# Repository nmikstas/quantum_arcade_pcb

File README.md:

# quantum_arcade_pcb
Reproduction of the Atari Quantum Arcade PCB. The PCB is designed with Kicad. This project is now complete and verified working!

# Folder Structure
* BOM - Bill of materials
* gerbers - Gerber files
* Quantum_1B_GAL - Design and programming files for the GAL IC located at location 1B
* quantum_arcade_pcb - Kicad design files

# PCB Specifications
* Layers: 2
* Dimensions: 293mm X 531mm
* Different PCB Design: 1
* PCB Thickness: 1.6mm
* Surface Finish: HASL
* Castellated Holes: No
* Copper Weight: 1oz.

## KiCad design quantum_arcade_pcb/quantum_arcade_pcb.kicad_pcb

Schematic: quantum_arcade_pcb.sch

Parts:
A_3: LM324A; DIP14
A_5: LS157A; DIP16
A_7, A_8: LS194; DIP16
A_10: 082; DIP8
B_1: 137290; DIP20
B_2/3: POKEY; DDIP40
B_5: LS157B; DIP16
B_6: AVG; DDIP40
B_7, B_8: LS194; DIP16
B_9: AM6012; DIP20
B_10: LF13201; DIP16
B_11, B_12: MC1495LB; DIP14
C2, C3, C9, C10, C11, C14, C15, C16, C17, C18, C19, C20, C26, C27, C28, C31, C33, C34, C35, C36, C39, C40: .1uF; GenComp
C4: .01uF; CapSmall
C5, C6, C22, C23: ?; GenComp
C7, C24: ?; CapSmall
C8, C25: .047uF; CapInt
C12, C29: 39pf; CapSmall
C13, C30, C32: 100pf; CapSmall
C21: .0018uF; CapSmall
C37: 150pF; CapSmall
C38: 39pF; CapSmall
C41: .01uF; GenComp
C42: 10pF; CapSmall
C44, C46: 100uf 35V; Cap2
C45, C48: 22uf 25V; Cap1
C47: 22uf 35V; Cap3
C49, C64, C65, C67, C68, C69, C70, C71, C72, C73, C75, C78, C79, C81, C91, C92, C93, C94, C95, C96, C97, C98, C99, C100, C101, C102, C103, C104, C105, C106, C107, C108, C109, C110, C111, C112, C113, C114, C115, C116, C117, C118, C119, C120, C121, C122, C123, C124, C125, C126, C127, C128, C129: .1uf; GenComp
C51, C61: 1000pf 100V; GenComp
C52, C53, C54, C55, C56, C57, C58, C59, C60, C62: 1uf 50V; Cap1
C63: 220pf; GenComp
C74: 1uf; Cap1
C76: 100pf 100V; CapSmall
C77: 39pf 100V; CapSmall
C80: .022uf; GenComp
C82: 100uf 25V; Cap2
C83, C84, C85, C86, C87, C88, C89, C90: .01uf 25V; GenComp
C130: .047uf; GenComp
CR1: 1N914; Diode
CR3, CR4, CR6: 1N100; Diode
CR5: 1N754A; Diode
CR7: LED
C_3: LM324A; DIP14
C_5: LS157B; DIP16
C_7, C_8: LS194; DIP16
C_9: Spare16; DIP16
C_11, C_12: MC1495LA; DIP14
D/E_4: LS245; DIP20
D/E_11, D/E_12: 082; DIP8
D_1: LS138; DIP16
D_2/3: POKEY; DDIP40
D_5, D_6: 2KX8_RAM; DDIP24
D_7: LS175C; DIP16
D_8: LS273; DIP20
D_9: DAC_8; DIP16
D_10: 082; DIP8
E/F_4: LS245; DIP20
E_1: LS244A; DIP20
E_2, E_3: 8KX8_ROM; DIP28
E_5, E_6: 2KX8_RAM; DDIP24
E_7: LS157B; DIP16
E_9: Spare16; DIP16
E_10: LF13201; DIP16
F/H_4: LS04; DIP14
F/H_9: AM6012; DIP20
F_1: LS244B; DIP20
F_2, F_3: 8KX8_ROM; DIP28
F_5: LS32; DIP14
F_6: LS00; DIP14
F_7: S289; DIP16
F_8: LS175; DIP16
H/J_2, H/J_3: 8KX8_ROM; DIP28
H/J_4: LS138; DIP16
H_5: LS174; DIP16
H_6: S129; DIP16
H_7: LS00; DIP14
H_8: LS399; DIP16
J20: J20; EdgeCon
J_4: LS02; DIP14
J_5: S74; DIP14
J_6: LS42; DIP16
J_7: LS175A; DIP16
J_8: LS175B; DIP16
J_9: LS260; DIP14
J_10: LS04; DIP14
K/L_1: 68000; DIP64
K_2, K_3: 8KX8_ROM; DIP28
K_4: LS08; DIP14
K_5: LS27; DIP14
K_6, K_9: LS109; DIP16
K_7, K_8: LS32; DIP14
K_10: S86; DIP14
L1: 100uH; Ind
L2, L3, L4: 1uH; Ind
L_2, L_3: 8KX8_ROM; DIP28
L_4: LS74; DIP14
L_5: LS161; DIP16
L_6: LS14; DIP14
L_7: S260; DIP14
L_8: S02; DIP14
L_9: LS175; DIP16
M/N_12: TL082; DIP8
M_2, M_3: 2KX8_RAM; DDIP24
M_4: 06; DIP14
M_5, M_6, M_7: LS161; DIP16
M_8: LS191A; DIP16
M_9: LS244C; DIP20
N_1: LS245B; DIP20
N_2, N_3: 2KX8_RAM; DDIP24
N_4: S32; DIP14
N_5: LS273B; DIP20
N_6: S02; DIP14
N_7: LS164; DIP14
N_8: LS191A; DIP16
N_9: LS244C; DIP20
N_10: 4584B; DIP14
P_1: LS245A; DIP20
P_2, P_3: LS245C; DIP20
P_4: LS00; DIP14
P_5: LS74; DIP14
P_6: LS02; DIP14
P_7: LS163; DIP16
P_8: S04; DIP14
P_9: LS191A; DIP16
P_10: LS157B; DIP16
P_11: 4584B; DIP14
Q7, Q9, Q10, Q11, Q13, Q14, Q17: 2N3904; GenTrans
Q8, Q12: 2N3906; GenTrans
Q15, Q16: 2N6044; BigTrans
R20, R22, R56, R57: ?; GenComp
R26, R27, R55: 820; GenComp
R30, R31, R58, R85, R86, R89, R93, R95, R96, R106: 7.5K; GenComp
R32, R33, R38, R51, R59, R62, R63, R137, R138, R139, R149, R151, R152, R160, R161, R162: 470; GenComp
R34, R60: 2.7k; GenComp
R35, R54, R61: 680; GenComp
R36, R44, R45, R50, R64, R69, R70, R77, R131, R133, R135, R141: 2.2k; GenComp
R37, R39, R52, R65, R66, R78, R79: 3.9k; GenComp
R40, R46, R67, R73, R118, R120, R121, R122, R123, R124, R125, R126, R127, R128, R143, R163, R173, R177, R178, R215: 10k; GenComp
R41, R71: 5.6k; GenComp
R42, R43, R68, R72: 10k; PotBlk
R47, R74: 2K; PotBlk
R48, R75: 100k; GenComp
R49: 1.5k; GenComp
R53, R80, R119, R129, R147, R148, R153, R155, R156, R157, R158, R159, R166, R167, R168, R169, R170, R171, R172, R176, R205, R210, R214, R218, R219, R220, R221, R222: 1k; GenComp
R76, R140: 1.2k; GenComp
R81: 15K; GenComp
R82: 1K; GenComp
R83: 10K; GenComp
R84: 560; GenComp
R87, R91: 7.5k; GenComp
R88, R92: 200; PotBlk
R90, R94, R224, R225, R226: 100; GenComp
R97: 3.9K; GenComp
R108: 270; CapInt
R110, R111, R112, R113, R114, R115, R116, R117, R134, R145: 3.3k; GenComp
R130, R132: 1.8k; GenComp
R136: 6.8k; GenComp
R142, R188, R189, R190, R191, R192, R193, R194, R195, R196, R197, R198, R199, R200, R201, R202, R203, R216, R217: 4.7k; GenComp
R144: 22k; GenComp
R146: 510; GenComp
R164, R165, R179, R223: 220; GenComp
R174: 68k; GenComp
R175: 15k; GenComp
R180, R181, R182, R183, R184, R185, R186, R187: 100K; GenComp
R204, R206, R207, R208, R209, R211, R212, R213: 220k; GenComp
RV1, RV2: VDR; GenComp
R_2, R_10: LS74; DIP14
R_3: X2212; DIP18
R_4, R_5: LS393; DIP14
R_6: LS161; DIP16
SW1, SW2: SW_DIP_x08; DIP16
TP5V1, TP5V2, TP6.8V1, TP12M1: TP
TP+15V1: TP
TP-15V1: TP
TPAUD1, TPAUD2: TP
TPBLU1: TP
TPGND1, TPGND2, TPGND3: TP
TPGRN1: TP
TPRED1: TP
TPRESET1, TPRESET2: TP
TPWDDIS1: TP
TPXOUT1: TP
TPYOUT1: TP
VR1: L7815_; BigTrans
VR2: L7915_; BigTrans
Y1: 12.096MHz; Crystal

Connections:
1.5M: K_6.3 (K), K_6.13 (K), K_7.9, P_6.12, P_7.12 (QC), P_8.9
1HORIZCLK: C55.2, C85.2, J20.6, R112.2
1HORIZDIR: C53.2, C83.2, J20.H, R110.2
1VERTCLK: C59.2, C89.2, J20.5, R116.2
1VERTDIR: C57.2, C87.2, J20.F, R114.2
2HORIZCLK: C56.2, C86.2, J20.8, R113.2
2HORIZDIR: C54.2, C84.2, J20.C, R111.2
2VERTCLK: C60.2, C90.2, J20.7, R117.2
2VERTDIR: C58.2, C88.2, J20.D, R115.2
3M: L_7.12, N_7.8 (CLK), P_6.11, P_7.13 (QB)
6M: K/L_1.15 (CLK), L_7.3, P_5.3 (1CLK), P_5.11 (2CLK), P_7.14 (QA), R_2.3 (1CLK), R_2.11 (2CLK)
12M: A_7.11 (CK), A_8.11 (CK), B_7.11 (CK), B_8.11 (CK), C_7.11 (CK), C_8.11 (CK), K_6.4 (Cp), K_6.12 (Cp), K_9.4 (Cp), K_9.12 (Cp), L_5.2 (CLK), M_5.2 (CLK), M_6.2 (CLK), M_7.2 (CLK), M_8.14 (CK), P_7.2 (CLK), P_8.10, TP12M1.1, TP12M1.2
750KHZ: P_7.11 (QD), R_5.1 (1CK)
+5V: A_5.16 (VCC), A_7.16 (VCC), A_8.16 (VCC), B_1.20 (Vcc), B_2/3.17 (VCC), B_5.16 (VCC), B_6.37 (VDD), B_7.16 (VCC), B_8.16 (VCC), B_9.20 (VCC), C2.1, C5.2, C19.1, C22.2, C39.1, C71.2, C75.1, C82.1, C96.1, C97.1, C98.1, C99.1, C100.1, C101.1, C102.1, C103.1, C104.1, C105.1, C106.1, C107.1, C108.1, C109.1, C110.1, C111.1, C112.1, C113.1, C114.1, C115.1, C116.1, C117.1, C118.1, C119.1, C120.1, C121.1, C122.1, C123.1, C124.1, C125.1, C126.1, C127.1, C128.1, C129.1, CR6.1 (K), C_5.16 (VCC), C_7.16 (VCC), C_8.16 (VCC), C_9.14, D/E_4.20 (VCC), D_1.16 (VCC), D_2/3.17 (VCC), D_5.24 (VCC), D_6.24 (VCC), D_7.16 (VCC), D_8.20 (VCC), D_9.13 (V+), E/F_4.20 (VCC), E_1.20 (VCC), E_2.1 (VPP), E_2.27 (~PGM), E_2.28 (VCC), E_3.1 (VPP), E_3.27 (~PGM), E_3.28 (VCC), E_5.24 (VCC), E_6.24 (VCC), E_7.16 (VCC), E_9.14, F/H_4.14 (VCC), F/H_9.20 (VCC), F_1.20 (VCC), F_2.1 (VPP), F_2.27 (~PGM), F_2.28 (VCC), F_3.1 (VPP), F_3.27 (~PGM), F_3.28 (VCC), F_5.14 (VCC), F_6.14 (VCC), F_7.16 (VCC), F_8.16 (VCC), H/J_2.1 (VPP), H/J_2.27 (~PGM), H/J_2.28 (VCC), H/J_3.1 (VPP), H/J_3.27 (~PGM), H/J_3.28 (VCC), H/J_4.16 (VCC), H_5.16 (VCC), H_6.16 (VCC), H_7.14 (VCC), H_8.16 (VCC), J20.2, J20.21, J20.B, J20.Y, J_4.14 (VCC), J_5.14 (VCC), J_6.16 (VCC), J_7.16 (VCC), J_8.16 (VCC), J_9.14 (VCC), J_10.14 (VCC), K/L_1.14 (VCC), K/L_1.49 (VCC), K_2.1 (VPP), K_2.27 (~PGM), K_2.28 (VCC), K_3.1 (VPP), K_3.27 (~PGM), K_3.28 (VCC), K_4.14 (VCC), K_5.14 (VCC), K_6.16 (VCC), K_7.14 (VCC)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
+6V: B_11.1, B_12.1, C32.1, C49.1, CR5.1 (K), C_11.1, C_12.1, R108.1, TP6.8V1.1, TP6.8V1.2
+10V: C74.1, J20.18, J20.E, M/N_12.8 (V+), R173.2
+15V: A_3.4 (V+), A_10.8 (VCC), B_10.13, B_11.2, B_12.2, C9.2, C11.2, C15.2, C18.1, C26.2, C28.2, C33.2, C36.1, C45.1, C92.1, C94.1, CR3.1 (K), C_3.4 (V+), D/E_11.8 (VCC), D/E_12.8 (VCC), D_10.8 (VCC), E_10.13, Q8.1 (E), R44.2, R45.2, R53.1, R69.2, R70.2, R80.1, R82.2, R95.1, R96.1, R108.2, TP+15V1.1, TP+15V1.2, VR1.3 (OUT)
+24V: C44.1, J20.3, J20.X, VR1.1 (IN)
-15V: A_3.11 (V-), A_10.4 (VSS), B_9.17 (V-), B_10.4, B_11.7, B_12.7, C3.2, C6.2, C10.2, C14.2, C16.2, C17.1, C20.2, C23.2, C27.2, C31.2, C34.2, C35.1, C40.1, C41.1, C48.2, C91.1, C93.1, CR4.2 (A), C_3.11 (V-), C_9.1, C_11.7, C_12.7, D/E_11.4 (VSS), D/E_12.4 (VSS), D_9.3 (V-), D_10.4 (VSS), E_9.1, E_10.4, F/H_9.17 (V-), TP-15V1.1, TP-15V1.2, VR2.3 (VO)
-24V: C46.2, C47.2, J20.4, J20.W, VR2.2 (VI)
A1: E_1.13 (I1b), K/L_1.29 (A1)
A2: E_1.11 (I0b), K/L_1.30 (A2)
A3: F_1.13 (I1b), K/L_1.31 (A3)
A4: F_1.11 (I0b), K/L_1.32 (A4)
A5: E_1.2 (I0a), K/L_1.33 (A5)
A6: F_1.2 (I0a), K/L_1.34 (A6)
A7: E_1.17 (I3b), K/L_1.35 (A7)
A8: E_1.4 (I1a), K/L_1.36 (A8)
A9: F_1.4 (I1a), K/L_1.37 (A9)
A10: F_1.17 (I3b), K/L_1.38 (A10)
A11: E_1.15 (I2b), K/L_1.39 (A11)
A12: F_1.6 (I2a), K/L_1.40 (A12)
A13: E_1.6 (I2a), K/L_1.41 (A13)
A14: F_1.15 (I2b), K/L_1.42 (A14)
A15: F_1.8 (I3a), K/L_1.43 (A15)
A16: D_1.3 (C), H/J_4.2 (B), K/L_1.44 (A16)
A17: H/J_4.3 (C), K/L_1.45 (A17)
A18: B_1.7, K/L_1.46 (A18)
A19: B_1.6, K/L_1.47 (A19)
A20: B_1.5, K/L_1.48 (A20)
A21: B_1.4, K/L_1.50 (A21)
A22: B_1.3, D_1.5 (~G2B), K/L_1.51 (A22)
A23: B_1.2, D_1.4 (~G2A), K/L_1.52 (A23), N_4.1
AB1: B_2/3.36 (A0), C_5.14 (4A), D_2/3.36 (A0), E_1.7 (O1b), E_2.10 (A0), E_3.10 (A0), E_7.14 (4A), F_2.10 (A0), F_3.10 (A0), H/J_2.10 (A0), H/J_3.10 (A0), K_2.10 (A0), K_3.10 (A0), L_2.10 (A0), L_3.10 (A0), M_2.8 (A0), M_3.8 (A0), N_2.8 (A0), N_3.8 (A0), R_3.6 (A0)
AB2: B_2/3.35 (A1), C_5.11 (3A), D_2/3.35 (A1), E_1.9 (O0b), E_2.9 (A1), E_3.9 (A1), E_7.11 (3A), F_2.9 (A1), F_3.9 (A1), H/J_2.9 (A1), H/J_3.9 (A1), K_2.9 (A1), K_3.9 (A1), L_2.9 (A1), L_3.9 (A1), M_2.7 (A1), M_3.7 (A1), N_2.7 (A1), N_3.7 (A1), R_3.5 (A1)
AB3: B_2/3.34 (A2), C_5.5 (2A), D_2/3.34 (A2), E_2.8 (A2), E_3.8 (A2), E_7.5 (2A), F_1.7 (O1b), F_2.8 (A2), F_3.8 (A2), H/J_2.8 (A2), H/J_3.8 (A2), K_2.8 (A2), K_3.8 (A2), L_2.8 (A2), L_3.8 (A2), M_2.6 (A2), M_3.6 (A2), N_2.6 (A2), N_3.6 (A2), R_3.4 (A2)
AB4: B_2/3.33 (A3), C_5.2 (1A), D_2/3.33 (A3), E_2.7 (A3), E_3.7 (A3), E_7.2 (1A), F_1.9 (O0b), F_2.7 (A3), F_3.7 (A3), H/J_2.7 (A3), H/J_3.7 (A3), K_2.7 (A3), K_3.7 (A3), L_2.7 (A3), L_3.7 (A3), M_2.5 (A3), M_3.5 (A3), N_2.5 (A3), N_3.5 (A3), R_3.3 (A3)
AB5: B_5.14 (4A), D_2/3.30 (~CSO), E_1.18 (O0a), E_2.6 (A4), E_3.6 (A4), F/H_4.9, F_2.6 (A4), F_3.6 (A4), H/J_2.6 (A4), H/J_3.6 (A4), K_2.6 (A4), K_3.6 (A4), L_2.6 (A4), L_3.6 (A4), M_2.4 (A4), M_3.4 (A4), N_2.4 (A4), N_3.4 (A4), R_3.2 (A4)
AB6: B_5.11 (3A), E_2.5 (A5), E_3.5 (A5), F_1.18 (O0a), F_2.5 (A5), F_3.5 (A5), H/J_2.5 (A5), H/J_3.5 (A5), K_2.5 (A5), K_3.5 (A5), L_2.5 (A5), L_3.5 (A5), M_2.3 (A5), M_3.3 (A5), N_2.3 (A5), N_3.3 (A5), R_3.1 (A5)
AB7: B_5.5 (2A), E_1.3 (O3b), E_2.4 (A6), E_3.4 (A6), F_2.4 (A6), F_3.4 (A6), H/J_2.4 (A6), H/J_3.4 (A6), K_2.4 (A6), K_3.4 (A6), L_2.4 (A6), L_3.4 (A6), M_2.2 (A6), M_3.2 (A6), N_2.2 (A6), N_3.2 (A6), R_3.17 (A6)
AB8: B_5.2 (1A), E_1.16 (O1a), E_2.3 (A7), E_3.3 (A7), F_2.3 (A7), F_3.3 (A7), H/J_2.3 (A7), H/J_3.3 (A7), K_2.3 (A7), K_3.3 (A7), L_2.3 (A7), L_3.3 (A7), M_2.1 (A7), M_3.1 (A7), N_2.1 (A7), N_3.1 (A7), R_3.16 (A7)
AB9: A_5.14 (4A), E_2.25 (A8), E_3.25 (A8), F_1.16 (O1a), F_2.25 (A8), F_3.25 (A8), H/J_2.25 (A8), H/J_3.25 (A8), K_2.25 (A8), K_3.25 (A8), L_2.25 (A8), L_3.25 (A8), M_2.23 (A8), M_3.23 (A8), N_2.23 (A8), N_3.23 (A8)
AB10: A_5.2 (1A), E_2.24 (A9), E_3.24 (A9), F_1.3 (O3b), F_2.24 (A9), F_3.24 (A9), H/J_2.24 (A9), H/J_3.24 (A9), K_2.24 (A9), K_3.24 (A9), L_2.24 (A9), L_3.24 (A9), M_2.22 (A9), M_3.22 (A9), N_2.22 (A9), N_3.22 (A9)
AB11: A_5.5 (2A), E_1.5 (O2b), E_2.21 (A10), E_3.21 (A10), F_2.21 (A10), F_3.21 (A10), H/J_2.21 (A10), H/J_3.21 (A10), K_2.21 (A10), K_3.21 (A10), L_2.21 (A10), L_3.21 (A10), M_2.19 (A10), M_3.19 (A10), N_2.19 (A10), N_3.19 (A10)
AB12: A_5.11 (3A), E_2.23 (A11), E_3.23 (A11), F_1.14 (O2a), F_2.23 (A11), F_3.23 (A11), H/J_2.23 (A11), H/J_3.23 (A11), K_2.23 (A11), K_3.23 (A11), L_2.23 (A11), L_3.23 (A11)
AB13: E_1.14 (O2a), E_2.2 (A12), E_3.2 (A12), F_2.2 (A12), F_3.2 (A12), H/J_2.2 (A12), H/J_3.2 (A12), K_2.2 (A12), K_3.2 (A12), L_2.2 (A12), L_3.2 (A12)
AB14: D_1.1 (A), F_1.5 (O2b)
AB15: D_1.2 (B), F_1.12 (O3a), H/J_4.1 (A)
AM1: C_5.12 (4Y), D_5.8 (A0), D_6.8 (A0), E_5.8 (A0), E_6.8 (A0)
AM2: C_5.9 (3Y), D_5.7 (A1), D_6.7 (A1), E_5.7 (A1), E_6.7 (A1)
AM3: C_5.7 (2Y), D_5.6 (A2), D_6.6 (A2), E_5.6 (A2), E_6.6 (A2)
AM4: C_5.4 (1Y), D_5.5 (A3), D_6.5 (A3), E_5.5 (A3), E_6.5 (A3)
AM5: B_5.12 (4Y), D_5.4 (A4), D_6.4 (A4), E_5.4 (A4), E_6.4 (A4)
AM6: B_5.9 (3Y), D_5.3 (A5), D_6.3 (A5), E_5.3 (A5), E_6.3 (A5)
AM7: B_5.7 (2Y), D_5.2 (A6), D_6.2 (A6), E_5.2 (A6), E_6.2 (A6)
AM8: B_5.4 (1Y), D_5.1 (A7), D_6.1 (A7), E_5.1 (A7), E_6.1 (A7)
AM9: A_5.12 (4Y), D_5.23 (A8), D_6.23 (A8), E_5.23 (A8), E_6.23 (A8)
AM10: A_5.4 (1Y), D_5.22 (A9), D_6.22 (A9), E_5.22 (A9), E_6.22 (A9)
AM11: A_5.7 (2Y), D_5.19 (A10), D_6.19 (A10), E_5.19 (A10), E_6.19 (A10)
AREF: A_3.5 (+), C78.2, C_3.10 (+), R204.2
AS: D_1.6 (G1), F/H_4.2, P_5.10 (~1PRE_), R_2.10 (~1PRE_)
AUDIO+: A_3.8, J20.13, R207.1, R208.2, TPAUD1.1, TPAUD1.2
BLUE: J20.17, R225.2, TPBLU1.1, TPBLU1.2
CNTR: K_7.4, K_9.6 (Q), L_7.11
COINAUX: J20.L, R159.2, R162.1
COINCONTL: C72.1, J20.15, Q15.2 (C)
COINCONTR: C73.1, J20.S, Q16.2 (C)
COINL: J20.J, R151.1, R155.2
COINR: J20.9, R152.1, R156.2
CS: B_2/3.31 (CS), D_2/3.31 (CS), J_4.10
D0: K/L_1.5 (D0), N_1.15 (B3)
D1: K/L_1.4 (D1), N_1.14 (B4)
D2: K/L_1.3 (D2), N_1.13 (B5)
D3: K/L_1.2 (D3), N_1.12 (B6)
D4: K/L_1.1 (D4), N_1.11 (B7)
D5: K/L_1.64 (D5), N_1.18 (B0)
D6: K/L_1.63 (D6), N_1.17 (B1)
D7: K/L_1.62 (D7), N_1.16 (B2)
D8: K/L_1.61 (D8), P_1.18 (B0)
D9: K/L_1.60 (D9), P_1.17 (B1)
D10: K/L_1.59 (D10), P_1.16 (B2)
D11: K/L_1.58 (D11), P_1.15 (B3)
D12: K/L_1.57 (D12), P_1.14 (B4)
D13: K/L_1.56 (D13), P_1.13 (B5)
D14: K/L_1.55 (D14), P_1.12 (B6)
D15: K/L_1.54 (D15), P_1.11 (B7)
DB0: B_2/3.38 (D0), D/E_4.11 (B7), D_2/3.38 (D0), F_7.4 (I0), M_9.14 (O2a), N_1.5 (A3), N_5.8 (D3), N_9.14 (O2a), P_3.16 (B2), R_3.12 (IO1)
DB1: B_2/3.39 (D1), D/E_4.12 (B6), D_2/3.39 (D1), F_7.6 (I1), M_9.12 (O3a), N_1.6 (A4), N_5.3 (D0), N_9.12 (O3a), P_3.14 (B4), R_3.13 (IO2)
DB2: B_2/3.40 (D2), D/E_4.13 (B5), D_2/3.40 (D2), F_7.10 (I2), M_9.16 (O1a), N_1.7 (A5), N_5.7 (D2), N_9.16 (O1a), P_3.12 (B6), R_3.14 (IO3)
DB3: B_2/3.2 (D3), D/E_4.14 (B4), D_2/3.2 (D3), F_7.12 (I3), M_9.18 (O0a), N_1.8 (A6), N_5.4 (D1), N_9.18 (O0a), P_3.11 (B7), R_3.15 (IO4)
DB4: B_2/3.3 (D4), D/E_4.15 (B3), D_2/3.3 (D4), M_9.5 (O2b), N_1.9 (A7), N_5.14 (D5), N_9.5 (O2b), P_3.13 (B5)
DB5: B_2/3.4 (D5), D/E_4.16 (B2), D_2/3.4 (D5), M_9.3 (O3b), N_1.2 (A0), N_5.13 (D4), N_9.3 (O3b), P_3.15 (B3)
DB6: B_2/3.5 (D6), D/E_4.17 (B1), D_2/3.5 (D6), M_9.7 (O1b), N_1.3 (A1), N_5.18 (D7), N_9.7 (O1b), P_3.17 (B1)
DB7: B_2/3.6 (D7), D/E_4.18 (B0), D_2/3.6 (D7), M_9.9 (O0b), N_1.4 (A2), N_5.17 (D6), N_9.9 (O0b), P_3.18 (B0)
DB8: E/F_4.11 (B7), P_1.2 (A0), P_2.16 (B2)
DB9: E/F_4.12 (B6), P_1.3 (A1), P_2.14 (B4)
DB10: E/F_4.13 (B5), P_1.4 (A2), P_2.12 (B6)
DB11: E/F_4.14 (B4), P_1.5 (A3), P_2.11 (B7)
DB12: E/F_4.15 (B3), P_1.6 (A4), P_2.13 (B5)
DB13: E/F_4.16 (B2), P_1.7 (A5), P_2.15 (B3)
DB14: E/F_4.17 (B1), P_1.8 (A6), P_2.17 (B1)
DB15: E/F_4.18 (B0), P_1.9 (A7), P_2.18 (B0)
DVG0: A_7.6 (D), A_8.6 (D), D/E_4.9 (A7), D_5.9 (D0), D_6.9 (D0)
DVG1: A_7.5 (C), A_8.5 (C), D/E_4.8 (A6), D_5.10 (D1), D_6.10 (D1)
DVG2: A_7.4 (B), A_8.4 (B), D/E_4.7 (A5), D_5.11 (D2), D_6.11 (D2)
DVG3: A_7.3 (A), A_8.3 (A), D/E_4.6 (A4), D_5.13 (D3), D_6.13 (D3)
DVG4: C_7.6 (D), C_8.6 (D), D/E_4.5 (A3), D_5.14 (D4), D_6.14 (D4)
DVG5: C_7.5 (C), C_8.5 (C), D/E_4.4 (A2), D_5.15 (D5), D_6.15 (D5)
DVG6: C_7.4 (B), C_8.4 (B), D/E_4.3 (A1), D_5.16 (D6), D_6.16 (D6)
DVG7: C_7.3 (A), C_8.3 (A), D/E_4.2 (A0), D_5.17 (D7), D_6.17 (D7)
DVG8: B_7.6 (D), B_8.6 (D), E/F_4.9 (A7), E_5.9 (D0), E_6.9 (D0)
DVG9: B_7.5 (C), B_8.5 (C), E/F_4.8 (A6), E_5.10 (D1), E_6.10 (D1)
DVG10: B_7.4 (B), B_8.4 (B), E/F_4.7 (A5), E_5.11 (D2), E_6.11 (D2)
DVG11: B_7.3 (A), B_8.3 (A), E/F_4.6 (A4), E_5.13 (D3), E_6.13 (D3)
DVG12: E/F_4.5 (A3), E_5.14 (D4), E_6.14 (D4), J_7.4 (D0), J_8.5 (D1)
DVG13: E/F_4.4 (A2), E_5.15 (D5), E_6.15 (D5), J_7.12 (D2), J_8.12 (D2)
DVG14: E/F_4.3 (A1), E_5.16 (D6), E_6.16 (D6), J_7.13 (D3), J_8.13 (D3)
DVG15: E/F_4.2 (A0), E_5.17 (D7), E_6.17 (D7), J_7.5 (D1), J_8.4 (D0)
DVX2: A_8.14 (QB), B_9.11 (B11), C_9.13
DVX3: A_8.15 (QA), B_9.10 (B10), C_8.7 (L), C_9.12
DVX4: B_9.9 (B9), C_8.12 (QD), C_9.11
DVX5: B_9.8 (B8), C_8.13 (QC), C_9.10
DVX6: B_9.7 (B7), C_8.14 (QB), C_9.9
DVX7: B_8.7 (L), B_9.6 (B6), C_8.15 (QA), C_9.8
DVX8: B_8.12 (QD), B_9.5 (B5), C_9.7
DVX9: B_8.13 (QC), B_9.4 (B4), C_9.6
DVX10: B_8.14 (QB), B_9.3 (B3), C_9.5, K_10.9
DVX11: B_8.15 (QA), J_10.9, K_10.10
DVY0: A_7.12 (QD), B_6.32 (DVY0), D_7.12 (D2), D_8.14 (D5)
DVY1: A_7.13 (QC), B_6.31 (DVY1), D_7.13 (D3), D_8.13 (D4)
DVY2: A_7.14 (QB), B_6.30 (DVY2), D_7.5 (D1), D_8.18 (D7), E_9.13, F/H_9.11 (B11)
DVY3: A_7.15 (QA), B_6.7 (DVY3), C_7.7 (L), D_7.4 (D0), D_8.17 (D6), E_9.12, F/H_9.10 (B10)
DVY4: B_6.8 (DVY4), C_7.12 (QD), D_8.8 (D3), E_9.11, F/H_9.9 (B9), F_8.13 (D3)
DVY5: B_6.9 (DVY5), C_7.13 (QC), D_8.7 (D2), E_9.10, F/H_9.8 (B8), F_8.12 (D2)
DVY6: B_6.10 (DVY6), C_7.14 (QB), D_8.4 (D1), E_9.9, F/H_9.7 (B7), F_8.5 (D1)
DVY7: B_6.11 (DVY7), B_7.7 (L), C_7.15 (QA), D_8.3 (D0), E_9.8, F/H_9.6 (B6), F_8.4 (D0)
DVY8: B_6.12 (DVY8), B_7.12 (QD), E_9.7, F/H_9.5 (B5), L_9.13 (D3)
DVY9: B_6.13 (DVY9), B_7.13 (QC), E_9.6, F/H_9.4 (B4), L_9.12 (D2)
DVY10: B_6.29 (DVY10), B_7.14 (QB), E_9.5, F/H_9.3 (B3), K_10.5, L_9.4 (D0), L_9.5 (D1)
DVY11: B_6.28 (DVY11), B_7.15 (QA), J_10.3, K_8.10, K_10.4
DVY12: J_7.2 (Q0), K_8.4
E: B_2/3.7 (PHI2), D_2/3.7 (PHI2), K/L_1.20 (E)
FC0: B_1.11, K/L_1.28 (FC0)
FC1: B_1.9, K/L_1.27 (FC1)
FC2: B_1.8, K/L_1.26 (FC2)
FLIP: N_5.5 (Q1), P_10.1 (S)
GND: A_3.3 (+), A_3.10 (+), A_5.8 (GND), A_5.15 (E), A_7.7 (L), A_7.8 (GND), A_8.7 (L), A_8.8 (GND), A_10.3 (+), A_10.5 (+), B_1.10 (GND), B_2/3.1 (GND), B_5.8 (GND), B_5.15 (E), B_6.14 (GND), B_6.27 (DVY12), B_7.8 (GND), B_8.8 (GND), B_9.1 (B1), B_9.12 (B12), B_9.13 (GND), B_9.19 (~IO), B_10.5, C2.2, C3.1, C4.1, C5.1, C6.1, C7.1, C9.1, C10.1, C11.1, C14.1, C15.1, C16.1, C17.2, C18.2, C19.2, C20.1, C21.1, C22.1, C23.1, C24.1, C26.1, C27.1, C28.1, C31.1, C33.1, C34.1, C35.2, C36.2, C39.2, C40.2, C42.1, C44.2, C45.2, C46.1, C47.1, C48.1, C49.2, C51.2, C52.2, C61.2, C62.2, C64.2, C65.2, C67.2, C68.2, C69.2, C70.2, C72.2, C73.2, C74.2, C75.2, C77.2, C78.1, C82.2, C83.1, C84.1, C85.1, C86.1, C87.1, C88.1, C89.1, C90.1, C91.2, C92.2, C93.2, C94.2, C96.2, C97.2, C98.2, C99.2, C100.2, C101.2, C102.2, C103.2, C104.2, C105.2, C106.2, C107.2, C108.2, C109.2, C110.2, C111.2, C112.2, C113.2, C114.2, C115.2, C116.2, C117.2, C118.2, C119.2, C120.2, C121.2, C122.2, C123.2, C124.2, C125.2, C126.2, C127.2, C128.2, C129.2, CR1.2 (A)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
GO: J_4.11, K_7.6, L_5.7 (EP), L_5.10 (ET)
GREEN: J20.V, R226.2, TPGRN1.1, TPGRN1.2
INVERTX: B_10.16, J_10.13, N_5.19 (Q7)
INVERTY: E_10.16, J_10.11, N_5.16 (Q6)
MB0: E_3.11 (D0), F_3.11 (D0), H/J_3.11 (D0), K_3.11 (D0), L_3.11 (D0), M_3.9 (D0), N_3.9 (D0), P_3.4 (A2)
MB1: E_3.12 (D1), F_3.12 (D1), H/J_3.12 (D1), K_3.12 (D1), L_3.12 (D1), M_3.10 (D1), N_3.10 (D1), P_3.6 (A4)
MB2: E_3.13 (D2), F_3.13 (D2), H/J_3.13 (D2), K_3.13 (D2), L_3.13 (D2), M_3.11 (D2), N_3.11 (D2), P_3.8 (A6)
MB3: E_3.15 (D3), F_3.15 (D3), H/J_3.15 (D3), K_3.15 (D3), L_3.15 (D3), M_3.13 (D3), N_3.13 (D3), P_3.9 (A7)
MB4: E_3.16 (D4), F_3.16 (D4), H/J_3.16 (D4), K_3.16 (D4), L_3.16 (D4), M_3.14 (D4), N_3.14 (D4), P_3.7 (A5)
MB5: E_3.17 (D5), F_3.17 (D5), H/J_3.17 (D5), K_3.17 (D5), L_3.17 (D5), M_3.15 (D5), N_3.15 (D5), P_3.5 (A3)
MB6: E_3.18 (D6), F_3.18 (D6), H/J_3.18 (D6), K_3.18 (D6), L_3.18 (D6), M_3.16 (D6), N_3.16 (D6), P_3.3 (A1)
MB7: E_3.19 (D7), F_3.19 (D7), H/J_3.19 (D7), K_3.19 (D7), L_3.19 (D7), M_3.17 (D7), N_3.17 (D7), P_3.2 (A0)
MB8: E_2.11 (D0), F_2.11 (D0), H/J_2.11 (D0), K_2.11 (D0), L_2.11 (D0), M_2.9 (D0), N_2.9 (D0), P_2.4 (A2)
MB9: E_2.12 (D1), F_2.12 (D1), H/J_2.12 (D1), K_2.12 (D1), L_2.12 (D1), M_2.10 (D1), N_2.10 (D1), P_2.6 (A4)
MB10: E_2.13 (D2), F_2.13 (D2), H/J_2.13 (D2), K_2.13 (D2), L_2.13 (D2), M_2.11 (D2), N_2.11 (D2), P_2.8 (A6)
MB11: E_2.15 (D3), F_2.15 (D3), H/J_2.15 (D3), K_2.15 (D3), L_2.15 (D3), M_2.13 (D3), N_2.13 (D3), P_2.9 (A7)
MB12: E_2.16 (D4), F_2.16 (D4), H/J_2.16 (D4), K_2.16 (D4), L_2.16 (D4), M_2.14 (D4), N_2.14 (D4), P_2.7 (A5)
MB13: E_2.17 (D5), F_2.17 (D5), H/J_2.17 (D5), K_2.17 (D5), L_2.17 (D5), M_2.15 (D5), N_2.15 (D5), P_2.5 (A3)
MB14: E_2.18 (D6), F_2.18 (D6), H/J_2.18 (D6), K_2.18 (D6), L_2.18 (D6), M_2.16 (D6), N_2.16 (D6), P_2.3 (A1)
MB15: E_2.19 (D7), F_2.19 (D7), H/J_2.19 (D7), K_2.19 (D7), L_2.19 (D7), M_2.17 (D7), N_2.17 (D7), P_2.2 (A0)
NORM: F_6.5, J_4.5, J_5.9 (2Q)
unnamed: A_3.2 (-), R208.1, R209.2
unnamed: A_3.6 (-), B_2/3.37 (AUD), C130.1, R205.2
unnamed: A_3.7, C79.1, C130.2, R205.1
unnamed: A_3.9 (-), R206.1, R207.2, R213.2
unnamed: A_5.3 (1B), B_6.19 (AVG10)
unnamed: A_5.6 (2B), B_6.20 (AVG11)
unnamed: A_5.10 (3B), B_6.21 (AVG12)
unnamed: A_5.13 (4B), B_6.18 (AVG9)
unnamed: A_7.9 (S0), B_7.9 (S0), C_7.9 (S0), L_6.10
unnamed: A_7.10 (S1), B_7.10 (S1), C_7.10 (S1), H_7.8
unnamed: A_8.9 (S0), B_8.9 (S0), C_8.9 (S0), L_6.12
unnamed: A_8.10 (S1), B_8.10 (S1), C_8.10 (S1), H_7.11
unnamed: A_10.1, B_10.14, R31.1
unnamed: A_10.2 (-), R30.1, R31.2
unnamed: A_10.7, B_10.3, B_10.11, C8.1, R30.2
unnamed: B_1.13, K_4.5
unnamed: B_2/3.8 (P6), R189.2, SW1.7
unnamed: B_2/3.9 (P7), R188.2, SW1.8
unnamed: B_2/3.10 (P4), R191.2, SW1.5
unnamed: B_2/3.11 (P5), R190.2, SW1.6
unnamed: B_2/3.12 (P2), R193.2, SW1.3
unnamed: B_2/3.13 (P3), R192.2, SW1.4
unnamed: B_2/3.14 (P0), R195.2, SW1.1
unnamed: B_2/3.15 (P1), R194.2, SW1.2
unnamed: B_2/3.30 (~CSO), F/H_4.8
unnamed: B_5.3 (1B), B_6.17 (AVG8)
unnamed: B_5.6 (2B), B_6.16 (AVG7)
unnamed: B_5.10 (3B), B_6.15 (AVG6)
unnamed: B_5.13 (4B), B_6.3 (AVG5)
unnamed: B_6.1 (AVG3), C_5.6 (2B)
unnamed: B_6.2 (AVG4), C_5.3 (1B)
unnamed: B_6.39 (AVG1), C_5.13 (4B)
unnamed: B_6.40 (AVG2), C_5.10 (3B)
unnamed: B_9.15 (VR-), R27.2
unnamed: B_10.1, J_10.12
unnamed: B_10.2, B_10.15, R32.2, R33.2
unnamed: B_11.4, B_11.9, R33.1
unnamed: B_11.5, R48.2, R49.2
unnamed: B_11.6, R48.1, R49.1
unnamed: B_11.10, R50.2
unnamed: B_11.11, R50.1
unnamed: B_11.8, B_11.12, R51.2
unnamed: B_11.3, B_11.13, R52.2
unnamed: B_12.4, B_12.9, R62.1
unnamed: B_12.5, R75.2, R76.2
unnamed: B_12.6, C32.2, R75.1, R76.1
unnamed: B_12.10, R77.2
unnamed: B_12.11, R77.1
unnamed: B_12.8, B_12.12, R78.2
unnamed: B_12.3, B_12.13, R79.2
unnamed: C4.2, R26.2
unnamed: C7.2, R20.1
unnamed: C12.1, C13.1, D/E_11.7, R46.1, R47.1, R47.2
unnamed: C12.2, C13.2, C_11.14, D/E_11.6 (-), R45.1, R46.2
unnamed: C21.2, R54.2
unnamed: C24.2, R56.1
unnamed: C25.1, D_10.7, E_10.3, E_10.11, R58.2
unnamed: C29.1, C30.1, D/E_12.7, R73.1, R74.1, R74.2
unnamed: C29.2, C30.2, C_12.14, D/E_12.6 (-), R70.1, R73.2
unnamed: C37.1, Q7.2 (B), R81.1
unnamed: C38.1, Q8.2 (B), R83.1
unnamed: C38.2, Q7.3 (C), R82.1, R83.2
unnamed: C41.2, D_9.16 (C)
unnamed: C42.2, CR1.1 (K), D_9.4 (IO), R85.1, R86.1, R87.2, R89.2, R91.2, R93.2
unnamed: C51.1, N_10.11, R118.2, R119.2
unnamed: C52.1, R118.1, R120.2, R122.2, R124.2, R126.2
unnamed: C53.1, N_10.1, R120.1
unnamed: C54.1, P_11.5, R121.2
unnamed: C55.1, N_10.3, R122.1
unnamed: C56.1, P_11.3, R123.2
unnamed: C57.1, N_10.5, R124.1
unnamed: C58.1, P_11.11, R125.2
unnamed: C59.1, N_10.13, R126.1
unnamed: C60.1, P_11.9, R127.2
unnamed: C61.1, P_11.1, R128.2, R129.2
unnamed: C62.1, R121.1, R123.1, R125.1, R127.1, R128.1
unnamed: C63.1, Q14.2 (B), R148.1
unnamed: C63.2, K_8.3, R148.2
unnamed: C64.1, M_9.15 (I2b), R156.1
unnamed: C65.1, M_9.17 (I3b), R155.1
unnamed: C67.1, M_9.11 (I0b), R153.1
unnamed: C68.1, M_9.2 (I0a), R157.1
unnamed: C69.1, M_9.4 (I1a), R158.1
unnamed: C70.1, M_9.8 (I3a), R159.1
unnamed: C71.1, N_5.1 (C), R163.2
unnamed: C76.1, Q17.2 (B), R177.1, R178.2, Y1.2
unnamed: C76.2, C77.1, L1.1, P_8.11, Q17.1 (E)
unnamed: C79.2, R206.2
unnamed: C80.1, C_3.6 (-), R211.1, R212.2
unnamed: C80.2, C81.1, C_3.7, R212.1
unnamed: C81.2, R213.1
unnamed: C95.1, C_3.8, R210.1
unnamed: C95.2, R211.2
unnamed: CR6.2 (A), L_6.3, R176.1, TPRESET2.1, TPRESET2.2
unnamed: CR7.1 (A), R214.1
unnamed: C_3.9 (-), D_2/3.37 (AUD), R210.2
unnamed: C_9.15, R22.2
unnamed: C_11.2, D/E_11.5 (+), R41.2, R44.1
unnamed: C_11.3, R39.2
unnamed: C_11.4, R34.2, R35.2
unnamed: C_11.5, R36.2
unnamed: C_11.6, R36.1
unnamed: C_11.9, R32.1
unnamed: C_11.10, R37.2
unnamed: C_11.11, R37.1
unnamed: C_11.8, C_11.12, R38.2
unnamed: C_11.13, R40.2
unnamed: C_12.2, D/E_12.5 (+), R69.1, R71.2
unnamed: C_12.3, R66.2
unnamed: C_12.4, R60.2, R61.2
unnamed: C_12.5, R64.2
unnamed: C_12.6, R64.1
unnamed: C_12.9, R59.1
unnamed: C_12.10, R65.2
unnamed: C_12.11, R65.1
unnamed: C_12.8, C_12.12, R63.2
unnamed: C_12.13, R67.2
unnamed: D/E_11.3 (+), R47.3, RV1.1
unnamed: D/E_12.3 (+), R74.3, RV2.1
unnamed: D_2/3.8 (P6), R197.1, SW2.7
unnamed: D_2/3.9 (P7), R196.1, SW2.8
unnamed: D_2/3.10 (P4), R199.1, SW2.5
unnamed: D_2/3.11 (P5), R198.1, SW2.6
unnamed: D_2/3.12 (P2), R201.1, SW2.3
unnamed: D_2/3.13 (P3), R200.1, SW2.4
unnamed: D_2/3.14 (P0), R203.1, SW2.1
unnamed: D_2/3.15 (P1), R202.1, SW2.2
unnamed: D_5.21 (~WE), D_6.21 (~WE), E_5.21 (~WE), E_6.21 (~WE), F_5.8
unnamed: D_7.2 (Q0), E_7.3 (1B)
unnamed: D_7.7 (Q1), E_7.6 (2B)
unnamed: D_7.9 (CK), K_8.11
unnamed: D_7.10 (Q2), E_7.13 (4B)
unnamed: D_7.15 (Q3), E_7.10 (3B)
unnamed: D_8.2 (Q0), D_9.5 (B1), R180.1
unnamed: D_8.5 (Q1), D_9.6 (B2), R181.1
unnamed: D_8.6 (Q2), D_9.7 (B3), R182.1
unnamed: D_8.9 (Q3), D_9.8 (B4), R183.1
unnamed: D_8.12 (Q4), D_9.11 (B7), R186.2
unnamed: D_8.15 (Q5), D_9.12 (B8), R187.2
unnamed: D_8.16 (Q6), D_9.9 (B5), R184.2
unnamed: D_8.19 (Q7), D_9.10 (B6), R185.2
unnamed: D_9.14 (VR+), R95.2, R96.2
unnamed: D_9.15 (VR-), R97.2
unnamed: D_10.1, E_10.14, R106.1
unnamed: D_10.2 (-), R58.1, R106.2
unnamed: E_7.4 (1Y), F_7.13 (A3)
unnamed: E_7.7 (2Y), F_7.14 (A2)
unnamed: E_7.9 (3Y), F_7.15 (A1)
unnamed: E_7.12 (4Y), F_7.1 (A0)
unnamed: E_9.15, R57.2
unnamed: E_10.1, J_10.10
unnamed: E_10.2, E_10.15, R59.2, R62.2
unnamed: F/H_4.4, P_4.5
unnamed: F/H_4.5, P_4.8
unnamed: F/H_9.15 (VR-), R55.2
unnamed: F_5.11, N_5.11 (CK)
unnamed: F_6.4, J_5.13 (~1CLR), L_7.6
unnamed: F_7.5 (D0), R136.2
unnamed: F_7.7 (D1), R134.2
unnamed: F_7.9 (D2), R132.2
unnamed: F_7.11 (D3), R130.2
unnamed: F_8.2 (Q0), H_8.4 (A2)
unnamed: F_8.7 (Q1), H_8.5 (B2)
unnamed: F_8.9 (CK), K_8.8
unnamed: F_8.10 (Q2), H_8.12 (C2)
unnamed: F_8.15 (Q3), H_8.13 (D2)
unnamed: H_5.2 (1Q), H_6.7 (A2)
unnamed: H_5.4 (2D), H_6.12 (O1), J_6.15 (A0)
unnamed: H_5.5 (2Q), H_6.5 (A0)
unnamed: H_5.7 (3Q), J_4.12
unnamed: H_5.9 (CK), K_6.7 (~Q)
unnamed: H_5.12 (5Q), H_6.6 (A1)
unnamed: H_5.13 (5D), H_6.11 (O2), J_6.14 (A1)
unnamed: H_5.14 (6D), H_6.9 (O4), K_6.15 (Cd)
unnamed: H_5.15 (6Q), H_6.4 (A3)
unnamed: H_6.15 (A7), J_4.13
unnamed: H_8.1 (WS), J_9.6
unnamed: H_8.2 (QA), J_9.1, R140.2
unnamed: H_8.7 (QB), J_9.2, R141.2
unnamed: H_8.10 (QC), J_9.3, R142.2
unnamed: H_8.15 (QD), J_9.12, R143.2
unnamed: J_4.1, K_9.2 (J)
unnamed: J_4.3, K_5.9, K_7.8
unnamed: J_4.4, L_5.9 (LD), M_5.9 (LD), M_6.9 (LD), M_7.9 (LD)
unnamed: J_5.6 (~1Q), K_4.12, K_9.1 (Cd), K_9.15 (Cd)
unnamed: J_9.5, K_8.1
unnamed: J_10.5, M_7.15 (RCO)
unnamed: K_4.1, R215.1, TPWDDIS1.1, TPWDDIS1.2
unnamed: K_4.2, L_4.6 (~1Q)
unnamed: K_4.3, L_4.2 (1D)
unnamed: K_4.13, K_9.7 (~Q)
unnamed: K_5.8, K_9.14 (J)
unnamed: K_6.2 (J), K_6.14 (J), L_7.5
unnamed: K_7.3, K_7.12, K_8.5
unnamed: K_8.2, N_6.13
unnamed: K_10.6, L_7.8
unnamed: K_10.8, L_7.9
unnamed: L1.2, R179.1
unnamed: L2.1, Q9.1 (E), R137.1
unnamed: L2.2, R224.1
unnamed: L3.1, Q10.1 (E), R138.1
unnamed: L3.2, R225.1
unnamed: L4.1, Q11.1 (E), R139.1
unnamed: L4.2, R226.1
unnamed: L_4.3 (1CLK), R_4.8 (2QD)
unnamed: L_4.5 (1Q), M_4.9, M_4.11
unnamed: L_4.11 (2CLK), P_8.1, R_6.15 (RCO)
unnamed: L_5.6 (D), M_5.14 (QA)
unnamed: L_5.5 (C), L_5.11 (QD)
unnamed: L_5.4 (B), L_5.12 (QC)
unnamed: L_5.3 (A), L_5.13 (QB)
unnamed: L_5.15 (RCO), M_5.7 (EP), M_5.10 (ET), M_6.7 (EP), M_7.7 (EP)
unnamed: L_7.1, L_8.10
unnamed: L_7.2, P_8.8
unnamed: L_8.6, M_8.4 (G), M_8.12 (M/M)
unnamed: L_8.5, L_8.13, P_8.13
unnamed: L_9.7 (Q1), M_8.10 (C)
unnamed: L_9.10 (Q2), M_8.1 (B)
unnamed: L_9.15 (Q3), M_8.15 (A)
unnamed: M/N_12.1, R174.1, R176.2, R223.2
unnamed: M/N_12.3 (+), R173.1, R174.2, R175.2
unnamed: M_4.1, N_5.15 (Q5)
unnamed: M_4.2, R165.2
unnamed: M_4.12, R164.2
unnamed: M_4.13, N_5.12 (Q4)
unnamed: M_5.6 (D), M_6.14 (QA)
unnamed: M_5.5 (C), M_5.11 (QD)
unnamed: M_5.4 (B), M_5.12 (QC)
unnamed: M_5.3 (A), M_5.13 (QB)
unnamed: M_5.15 (RCO), M_6.10 (ET)
unnamed: M_6.6 (D), M_7.14 (QA)
unnamed: M_6.5 (C), M_6.11 (QD)
unnamed: M_6.4 (B), M_6.12 (QC)
unnamed: M_6.3 (A), M_6.13 (QB)
unnamed: M_6.15 (RCO), M_7.10 (ET)
unnamed: M_7.3 (A), M_7.13 (QB)
unnamed: M_8.11 (LD), P_8.12
unnamed: N_4.3, R_2.2 (1D)
unnamed: N_4.6, R_3.11 (~WE)
unnamed: N_5.2 (Q0), R166.2, R167.2
unnamed: N_5.9 (Q3), R168.2, R169.2
unnamed: N_6.4, P_6.9
unnamed: N_6.11, N_7.11 (QF)
unnamed: N_6.12, N_7.10 (QE)
unnamed: N_8.2 (QB), N_9.8 (I3a)
unnamed: N_8.3 (QA), N_9.6 (I2a)
unnamed: N_8.5 (D/U), R_10.9 (2Q)
unnamed: N_8.6 (QC), N_9.4 (I1a)
unnamed: N_8.7 (QD), N_9.2 (I0a)
unnamed: N_8.14 (CK), P_10.12 (4Y), R_10.11 (2CLK)
unnamed: N_9.11 (I0b), P_9.7 (QD)
unnamed: N_9.13 (I1b), P_9.6 (QC)
unnamed: N_9.15 (I2b), P_9.3 (QA)
unnamed: N_9.17 (I3b), P_9.2 (QB)
unnamed: N_10.2, P_10.2 (1A)
unnamed: N_10.4, P_10.5 (2A)
unnamed: N_10.6, P_10.11 (3A)
unnamed: N_10.10, R119.1
unnamed: N_10.12, P_10.14 (4A)
unnamed: P_4.3, R_4.12 (2CLR), R_5.12 (2CLR)
unnamed: P_4.6, R172.1, R_3.7 (~CS)
unnamed: P_4.4, P_4.11, R170.1, R_3.9 (~STR)
unnamed: P_5.2 (1D), P_6.13
unnamed: P_5.6 (~1Q), P_6.6
unnamed: P_6.4, P_6.8
unnamed: P_8.2, R_6.9 (LD)
unnamed: P_9.5 (D/U), R_10.5 (1Q)
unnamed: P_10.3 (1B), P_11.6
unnamed: P_10.4 (1Y), R_10.2 (1D)
unnamed: P_10.6 (2B), P_11.4
unnamed: P_9.14 (CK), P_10.7 (2Y), R_10.3 (1CLK)
unnamed: P_10.9 (3Y), R_10.12 (2D)
unnamed: P_10.10 (3B), P_11.10
unnamed: P_10.13 (4B), P_11.8
unnamed: P_11.2, R129.1
unnamed: Q8.3 (C), R84.2, R85.2, R86.2
unnamed: Q9.2 (B), R130.1, R131.2
unnamed: Q10.2 (B), R132.1, R133.1
unnamed: Q11.2 (B), R134.1, R135.1, R136.1
unnamed: Q12.1 (E), Q13.2 (B), R146.1
unnamed: Q12.2 (B), Q14.3 (C), R140.1, R141.1, R142.1, R143.1, R144.2, R145.1
unnamed: Q15.1 (B), R167.1
unnamed: Q16.1 (B), R169.1
unnamed: R39.1, R42.3
unnamed: R41.1, R43.3
unnamed: R66.1, R68.3
unnamed: R71.1, R72.3
unnamed: R87.1, R88.3
unnamed: R89.1, R90.2
unnamed: R91.1, R92.3
unnamed: R93.1, R94.2
unnamed: R_4.1 (1CK), R_5.6 (1QD)
unnamed: R_4.6 (1QD), R_6.2 (CLK)
unnamed: R_4.13 (2CK), R_5.8 (2QD)
unnamed: R_5.13 (2CK), R_6.14 (QA)
OP0: H_6.3 (A4), J_5.2 (1D), J_7.10 (Q2), K_5.10
OP1: B_6.33 (OP1), H_6.2 (A5), J_7.15 (Q3)
OP2: H_6.1 (A6), J_7.7 (Q1), K_5.11, K_7.1, L_8.11
PL1LED: J20.N, R165.1
PL2LED: J20.14, R164.1
POR: L_6.4, L_6.5, P_4.13, R_4.2 (1CLR), R_5.2 (1CLR)
PR218: H/J_4.6 (G1), K/L_1.12 (~BBACK), K/L_1.13 (~BR), K/L_1.22 (~BERR), K/L_1.23 (~IPL2), K/L_1.24 (~IPL1), R218.2, R_2.1 (~1CLR), R_2.4 (~1PRE_), R_2.13 (~1CLR)
PR219: J_5.10 (~1PRE_), L_4.1 (~1CLR), L_4.13 (~1CLR), L_5.1 (C), M_5.1 (C), P_5.1 (~1CLR), P_5.4 (~1PRE_), P_5.13 (~1CLR), R219.2
PR220: P_7.3 (A), P_7.4 (B), P_7.5 (C), P_7.6 (D), P_7.7 (EP), P_7.9 (LD), P_7.10 (ET), R220.2, R_6.5 (C), R_6.7 (EP), R_6.10 (ET)
PR221: K_6.1 (Cd), K_6.5 (Sd), K_6.11 (Sd), K_9.5 (Sd), K_9.11 (Sd), M_6.1 (C), M_7.1 (C), M_7.4 (B), M_7.5 (C), M_7.6 (D), M_8.5 (D/U), N_7.9 (C), N_8.11 (LD), P_9.11 (LD), R221.2, R_10.1 (~1CLR), R_10.4 (~1PRE_), R_10.10 (~1PRE_), R_10.13 (~1CLR)
PR222: A_7.1 (C), A_7.2 (R), A_8.2 (R), B_7.1 (C), B_7.2 (R), B_8.2 (R), C_7.1 (C), C_7.2 (R), C_8.2 (R), J_7.1 (C), R222.2
RED: J20.T, R224.2, TPRED1.1, TPRED1.2
R\~W: D/E_4.1 (DIR), E/F_4.1 (DIR), E_1.8 (I3a), F_5.9, K/L_1.9 (R/~W), P_2.1 (DIR), P_3.1 (DIR)
R\~W~B: B_2/3.32 (R/~W), D_2/3.32 (R/~W), E_1.12 (O3a), F/H_4.11, N_1.1 (DIR), N_4.10, N_4.13, P_1.1 (DIR)
SCALE: J_4.6, L_7.4, L_8.4
SCALELO: D_8.11 (CK), K_7.11, L_9.9 (CK)
SELFTEST: J20.10, R149.1, R153.2
ST2: B_6.35 (ST2), H_5.3 (1D), H_6.10 (O3), J_6.13 (A2), L_8.8
ST3: B_6.38 (ST3), J_6.12 (A3), K_6.9 (~Q)
START1: J20.11, R158.2, R161.1
START2: J20.M, R157.2, R160.1
UPDATE: N_5.6 (Q2), P_4.12
VCTR: C37.2, H_8.9 (CLK), K_7.5, K_9.10 (Q), L_7.10, N_7.1 (A), N_7.2 (B), R81.2
VHALT: H_5.6 (3D), J_5.5 (1Q), M_9.6 (I2a)
XBIP: A_10.6 (-), B_9.18 (IO), B_10.10, C8.2, C_9.3, R92.1, R92.2
XCOR: B_11.14, R53.2, R60.1
XOUT: D/E_11.1, D/E_11.2 (-), J20.19, TPXOUT1.1, TPXOUT1.2
XREF: B_9.14 (VR+), C_9.16, R20.2, R26.1, R94.1
YBIP: C25.2, D_10.6 (-), E_9.3, E_10.10, F/H_9.18 (IO), R88.1, R88.2
YCOR: B_12.14, R34.1, R80.2
YOUT: D/E_12.1, D/E_12.2 (-), J20.20, TPYOUT1.1, TPYOUT1.2
YREF: E_9.16, F/H_9.14 (VR+), R54.1, R56.2, R90.1
Z0: H_8.14 (D1), J_8.7 (Q1), J_9.10
Z1: H_8.11 (C1), J_8.10 (Q2)
Z2: H_8.6 (B1), J_8.15 (Q3), J_9.8
Z3: H_8.3 (A1), J_8.2 (Q0), J_9.4
ZREF: Q9.3 (C), Q10.3 (C), Q11.3 (C), Q13.1 (E), R131.1, R133.2, R135.2, R147.2
~AS: B_1.1, F/H_4.1, K/L_1.6 (~AS), N_4.2
~AUDIO: A_3.1, J20.12, R209.1, TPAUD2.1, TPAUD2.2
~CENTER: B_10.9, E_10.9, K_4.11
~COLORAM: E_7.1 (S), F_5.1, H/J_4.13 (Y2)
~COLORAMWA: F_5.3, F_7.3 (WE)
~CONTROL: F_5.12, H/J_4.12 (Y3)
~DISRST: D_7.1 (C), D_8.1 (C), F_8.1 (C), H_5.1 (C), J_5.4 (~1PRE_), K_4.8, L_9.1 (C)
~DTACK: F/H_4.6, K/L_1.10 (~DTACK)
~DTACK2: K_4.6, P_4.9
~DVX11: B_9.2 (B2), C_9.4, J_10.8
~DVY11: E_9.4, F/H_9.2 (B2), J_10.4, K_8.13
~DVY12: J_7.3 (~Q0), K_7.13
~ENORM: F_6.6, H_7.9, H_7.12
~HALT: K/L_1.17 (~HALT), M_4.10, R216.2
~IRQ: K/L_1.25 (~IPL0), L_4.9 (2Q)
~I\O: B_1.18, H/J_4.4 (~G2A)
~I\OS: B_1.15, J_4.8
~LATCH1: A_8.1 (C), B_8.1 (C), C_8.1 (C), H_7.10, J_6.2 (1), J_7.9 (CK), J_8.1 (C), L_6.11
~LATCH3: H_7.13, J_6.4 (3), J_8.9 (CK), L_6.13
~LDS: K/L_1.8 (~LDS), N_4.9
~MDTACK: P_2.19 (CE), P_3.19 (CE), P_4.10, R_2.5 (1Q), R_2.12 (2D)
~NVRAM: B_1.19, F/H_4.3, N_4.4
~OP0: B_6.26 (~OP0), J_5.12 (2D), J_7.11 (~Q2)
~OP2: B_6.5 (~OP2), J_4.2, J_7.6 (~Q1)
~POR: L_4.4 (~1PRE_), L_6.6, P_4.1, P_7.1 (C), R_6.1 (C)
~RAM0: D_1.9 (Y6), N_2.18 (~CE), N_3.18 (~CE)
~RAM1: D_1.7 (Y7), M_2.18 (~CE), M_3.18 (~CE)
~RECALL: H/J_4.11 (Y4), R171.1, R_3.10 (~RC)
~RESET: K/L_1.18 (~RESET), K_4.10, M_4.8, R217.2
~ROM0: D_1.15 (Y0), E_2.20 (G), E_3.20 (G)
~ROM1: D_1.14 (Y1), F_2.20 (G), F_3.20 (G)
~ROM2: D_1.13 (Y2), H/J_2.20 (G), H/J_3.20 (G)
~ROM3: D_1.12 (Y3), K_2.20 (G), K_3.20 (G)
~ROM4: D_1.11 (Y4), L_2.20 (G), L_3.20 (G)
~R~\WB: E_2.22 (E), E_3.22 (E), F/H_4.10, F_2.22 (E), F_3.22 (E), H/J_2.22 (E), H/J_3.22 (E), K_2.22 (E), K_3.22 (E), L_2.22 (E), L_3.22 (E), M_2.20 (~OE), M_3.20 (~OE), N_2.20 (~OE), N_3.20 (~OE)
~STATCLK: K_8.6, K_8.9, K_8.12
~STOP: J_10.6, K_9.3 (K), K_9.13 (K)
~STROBE0: B_6.24 (~STROBE0), J_5.11 (2CLK), J_6.5 (4)
~STROBE1: B_6.34 (~STROBE1), J_6.6 (5), L_8.12
~STROBE2: B_6.4 (~STROBE2), J_6.7 (6), K_7.2
~STROBE3: J_5.3 (1CLK), J_6.9 (7), K_7.10
~SWITCHES: H/J_4.14 (Y1), M_9.1 (OEa), M_9.19 (OEb)
~TRACKBALL: H/J_4.15 (Y0), N_9.1 (OEa), N_9.19 (OEb)
~UDS: K/L_1.7 (~UDS), N_4.12
~V68K: A_5.1 (S), B_5.1 (S), C_5.1 (S), L_8.9, N_6.5, P_5.12 (2D), P_6.10
~VBUFEN: D/E_4.19 (CE), E/F_4.19 (CE), F_5.10, K_4.4, P_5.9 (2Q)
~VCTR: D_9.1 (TH), K_9.9 (~Q)
~VGGO: B_6.6 (~VGGO), H/J_4.9 (Y6), J_5.1 (~1CLR)
~VGRST: H/J_4.10 (Y5), K_4.9
~VMA: J_4.9, K/L_1.19 (~VMA)
~VMEM: B_1.16, N_6.6, P_6.5
~VPA: B_1.12, K/L_1.21 (~VPA), L_4.10 (~1PRE_)
~VRAM0: A_5.9 (3Y), D_5.18 (~CE), E_5.18 (~CE), F/H_4.13
~VRAM1: D_6.18 (~CE), E_6.18 (~CE), F/H_4.12
~WDCLR: H/J_4.7 (Y7), P_4.2
~WEL: F_5.2, F_5.13, M_3.21 (~WE), N_3.21 (~WE), N_4.5, N_4.8
~WEU: M_2.21 (~WE), N_2.21 (~WE), N_4.11
~Z1: J_8.11 (~Q2), J_9.9

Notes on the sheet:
POWER INPUT
CLOCK
POWER-ON RESET AND WATCHDOG
MICROPROCESSOR
ADDRESS BUS BUFFERS
BIDIRECTIONAL DATA BUS BUFFERS
ADDRESS DECODERS
PROGRAM RAM
DATA TRANSFER ACK GENERATOR
CHECK THIS!!!
PROGRAM ROM
Y-Axis Output
NOT LOADED
X-Axis Output
DAC Reference And Bipolar Current Sources
COIN DOOR AND CONTROL PANEL INPUT
TRACK BALL INPUT
NON-VOLATILE MEMORY
COIN DOOR AND CONTROL PANEL OUTPUT
AUDIO OUTPUT
COLOR MEMORY AND OUTPUT
VECTOR MEMORY ARBITRATOR
VECTOR MEMORY
BIDIRECTIONAL VECTOR MEMORY DATA BUFFERS
VECTOR DATA SHIFTERS
OPCODE AND INTENSITY LATCHES
VECTOR ADDRESS CONTROLLER
STATE MACHINE
Z INTENSITY
VECTOR TIMER
INTENSITY CORRECTION
VECTOR HALT FLAG
VECTOR FLAG
CENTER FLAG
NORMALIZATION FLAG
VECTOR SCALING
UNUSED

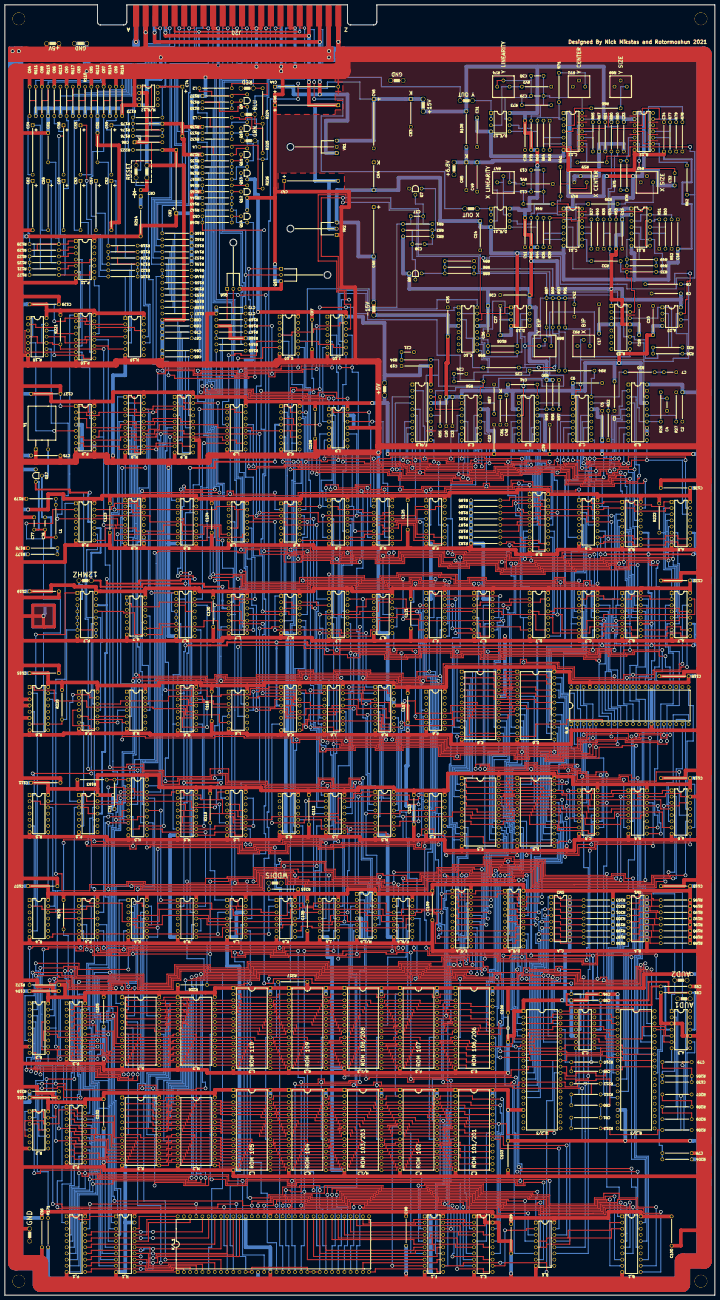
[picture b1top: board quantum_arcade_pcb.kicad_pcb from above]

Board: 2 copper layers, 292.1 x 530.9 mm, 482 parts (0 on the bottom side), 568 nets.

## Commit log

2021-07-28 Initial commit. Set up repository. Did initial project work
2021-07-29 Finished the first 2 pages of schematics
2021-07-30 Worked on schematic
2021-07-31 added schematic stuff
2021-08-02 Completed 5 schematic pages out of 14
2021-08-03 Completed 6 schematic pages out of 14
2021-08-05 Completed 8 pages of schematics
2021-08-06 Completed 9 pages of schematics
2021-08-07 Completed 10 pages of schematics
2021-08-08 Finished 13 of 14 schematic pages
2021-08-09 Finished initial schematic
2021-08-09 Fixed all schematic errors
2021-08-10 Placed all ICs on the PCB
2021-08-10 Placed several components
2021-08-11 133 components left to place
2021-08-11 80 components left to place
2021-08-12 50 components left to place
2021-08-13 25 components left to place
2021-08-15 Finished placing components
2021-08-17 1498 disconnected signals remain
2021-08-18 Added more traces
2021-08-18 1394 disconnected signals remain
2021-08-23 1110 unconnected signals remain
2021-09-03 Added more signal traces
2021-09-07 Added ground plane, 786 disconnected signals remain
2021-09-08 592 disconnedted signals remain
2021-09-10 542 disconnedted signals remain
2021-09-10 495 disconnedted signals remain
2021-09-11 388 disconnedted signals remain
2021-09-13 295 disconnedted signals remain
2021-09-13 208 disconnedted signals remain
2021-09-15 84 disconnected signals remain
2021-09-15 All signals connected
2021-09-26 Added gerbers
2021-10-13 Added filed for the 1B IC
2021-10-30 Fixed silkscreen issues and connected pin 1 of 7J to pullup
2021-11-05 Made final PCB changes
2021-11-06 Updated gerbers
2021-11-22 Updated the readme file
2021-11-28 Began working on the BOM
2021-11-29 Worked on the BOM
2021-12-14 Updated BOM
